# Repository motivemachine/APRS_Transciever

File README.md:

# APRS_Transciever
An in development design for a complete, standalone transciever for voice and aprs digital communication for the 2meter/70cm band. It is primarily based on the DRA818 radio module and controlled with an arduino. 

This project is made possible for amateur designers like me thanks to the work of:

markqvist and his APRS library:
https://github.com/markqvist/LibAPRS

darksidelemm and his DRA818 serial library:
https://github.com/darksidelemm/dra818

Progress:
Currently the basic Kicad schematic is complete, using an arduino nano and two bss183 mosfets to convert the 5v IO to 3.3v for the dRA818V. Resistors on Arduino Nano pins 4-7 form the DDS as used with LibAPRS. No other interfaces are yet included, but many are planned (gps, display, etc.)

Next steps:
After further breadboard testing, complete designs for the PCBs in Kicad. The first design will be for a single-sided PCB for etching at home and further development. A two layer production design will follow after any changes are made

Begin adding some other interfaces to the circuit, such as GPS, sh1106 OLED display, battery management circuits,and other useful telemetry

Firmware will mostly be based on the arduino libraries of others, but will be uploaded here as changes are made.

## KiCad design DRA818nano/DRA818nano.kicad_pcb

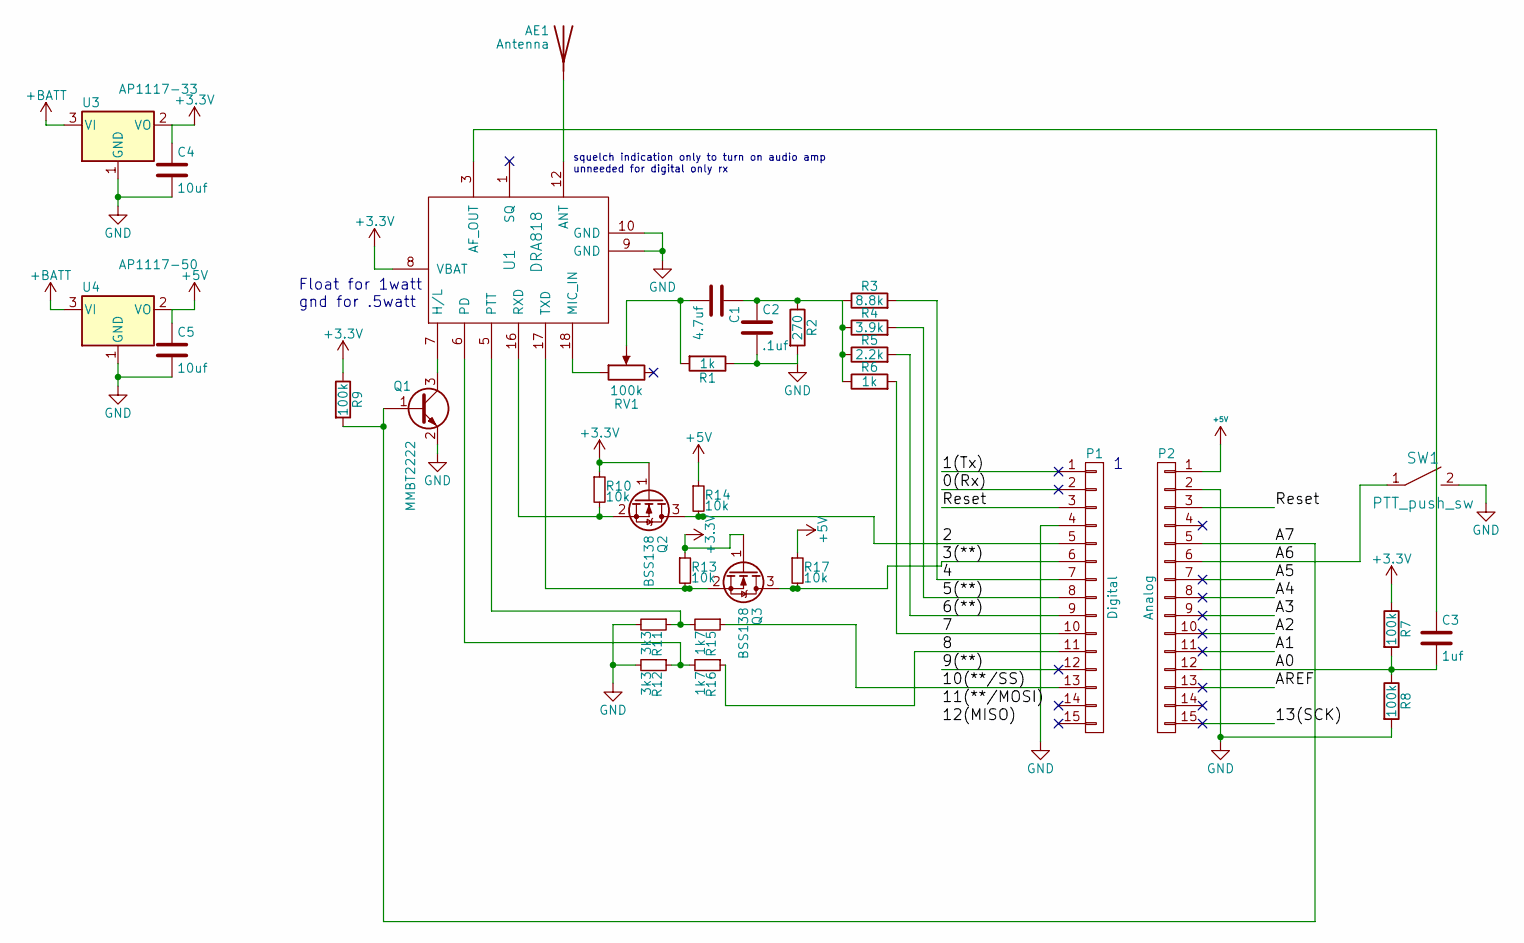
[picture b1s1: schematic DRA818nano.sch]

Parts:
AE1: Antenna; Pin_Header_Straight_1x01_Pitch2.54mm
C1: 4.7uf; C_0805
C2: .1uf; C_0805
C3: 1uf; C_0805
C4, C5: 10uf; C_0805
P1: Digital; Socket_Strip_Arduino_1x15
P2: Analog; Socket_Strip_Arduino_1x15
Q1: MMBT2222; SOT-23
Q2, Q3: BSS138; SOT-23
R1, R6: 1k; R_0805
R2: 270; R_0805
R3: 8.8k; R_0805
R4: 3.9k; R_0805
R5: 2.2k; R_0805
R7, R8, R9: 100k; R_0805
R10, R13, R14, R17: 10k; R_0805
R11, R12: 3k3; R_0805
R15, R16: 1k7; R_0805
RV1: 100k; Potentiometer_Trimmer_ACP_CA6v_Horizontal
SW1: PTT_push_sw; SW_PUSH_6mm_h7.3mm
U1: DRA818
U3: AP1117-33; SOT-223-3_TabPin2
U4: AP1117-50; SOT-223-3_TabPin2

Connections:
+3V3: C4.1, Q2.1 (G), Q3.1 (G), R7.1, R9.1, R10.1, R13.1, U1.8 (VBAT), U3.2 (VO)
+5V: C5.1, P2.1, R14.1, R17.1, U4.2 (VO)
+BATT: U3.3 (VI), U4.3 (VI)
/0(Rx): P1.2
/1(Tx): P1.1
/2: P1.5, Q2.3 (D), R14.2
/3(**): P1.6, Q3.3 (D), R17.2
/4: P1.7, R3.2
/5(**): P1.8, R4.2
/6(**): P1.9, R5.2
/7: P1.10, R6.2
/8: P1.11, R16.1
/9(**): P1.12
/10(**/SS): P1.13, R15.1
/13(SCK): P2.15
/A0: C3.2, P2.12, R7.2, R8.1
/A1: P2.11
/A2: P2.10
/A3: P2.9
/A4: P2.8
/A5: P2.7
/A6: P2.6, SW1.1
/A7: P2.5, Q1.1 (B), R9.2
/AREF: P2.13
/Reset: P1.3, P2.3
GND: C2.2, C4.2, C5.2, P1.4, P2.2, Q1.2 (E), R1.1, R2.2, R8.2, R11.2, R12.2, SW1.2, U1.9 (GND), U1.10 (GND), U3.1 (GND), U4.1 (GND)
unnamed: AE1.1, U1.12 (ANT)
unnamed: C1.1, C2.1, R2.1, R3.1, R4.1, R5.1, R6.1
unnamed: C1.2, R1.2, RV1.2
unnamed: C3.1, U1.3 (AF_OUT)
unnamed: Q1.3 (C), U1.7 (H/L)
unnamed: Q2.2 (S), R10.2, U1.16 (RXD)
unnamed: Q3.2 (S), R13.2, U1.17 (TXD)
unnamed: R11.1, R15.2, U1.5 (PTT)
unnamed: R12.1, R16.2, U1.6 (PD)
unnamed: RV1.1, U1.18 (MIC_IN)

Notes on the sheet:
Float for 1watt gnd for .5watt
squelch indication only to turn on audio amp unneeded for digital only rx

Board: 2 copper layers, 37 parts (0 on the bottom side), 26 nets, no tracks yet.

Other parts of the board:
P3, P4, P5, P6: CONN_01X01; 1pin_Nano

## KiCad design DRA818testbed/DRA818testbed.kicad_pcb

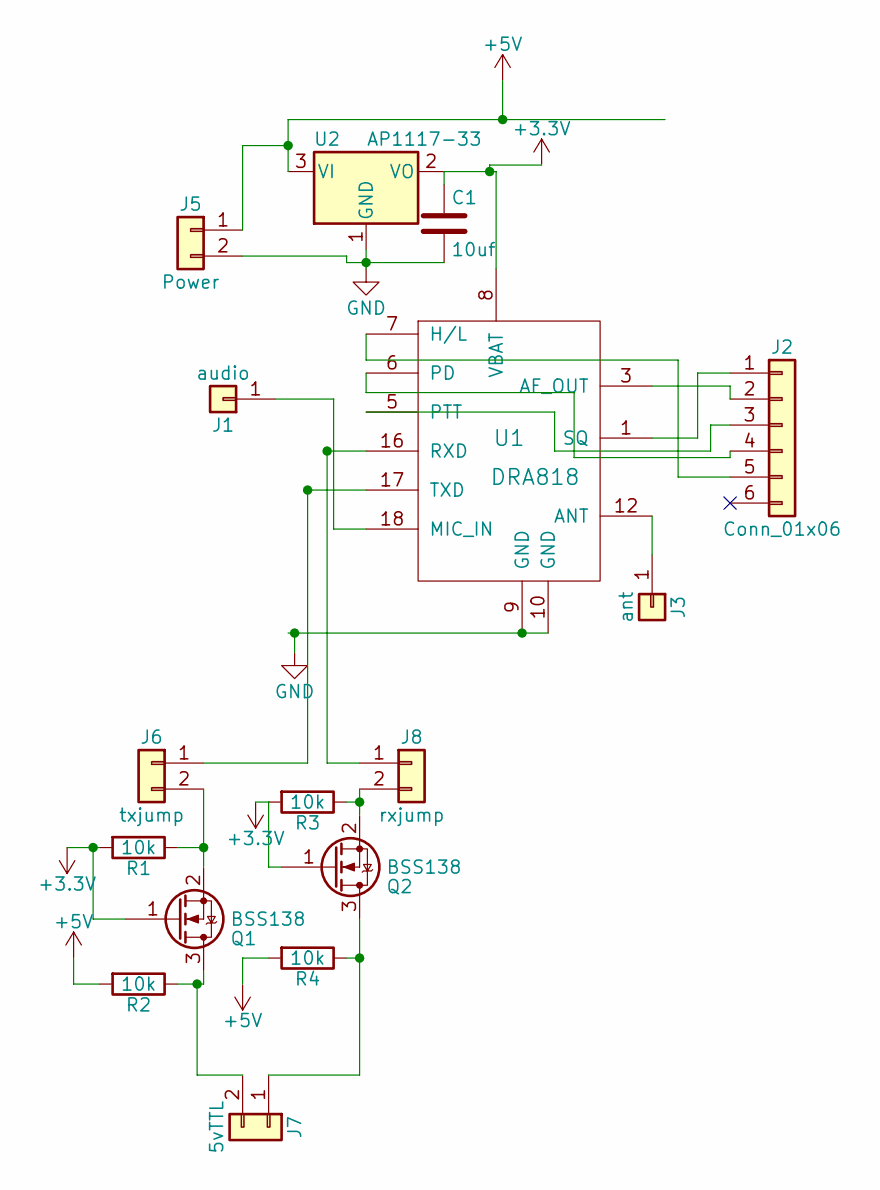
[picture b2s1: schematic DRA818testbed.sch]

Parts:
C1: 10uf; C_Disc_D8.0mm_W2.5mm_P5.00mm
J1: audio; Pin_Header_Straight_1x01_Pitch2.54mm
J2: Conn_01x06; Pin_Header_Straight_1x06_Pitch2.54mm
J3: ant; Pin_Header_Straight_1x01_Pitch2.54mm
J5: Power; Pin_Header_Straight_1x02_Pitch2.54mm
J6: txjump; Pin_Header_Straight_1x02_Pitch2.54mm
J7: 5vTTL; Pin_Header_Straight_1x02_Pitch2.54mm
J8: rxjump; Pin_Header_Straight_1x02_Pitch2.54mm
Q1, Q2: BSS138; SOT-23
R1, R2, R3, R4: 10k; R_0805
U1: DRA818
U2: AP1117-33; SOT-223-3_TabPin2

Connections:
+3V3: C1.1, Q1.1 (G), Q2.1 (G), R1.2, R3.2, U1.8 (VBAT), U2.2 (VO)
+5V: J5.1, R2.2, R4.2, U2.3 (VI)
GND: C1.2, J5.2, U1.9 (GND), U1.10 (GND), U2.1 (GND)
unnamed: J1.1, U1.18 (MIC_IN)
unnamed: J2.1, U1.1 (SQ)
unnamed: J2.2, U1.3 (AF_OUT)
unnamed: J2.3, U1.5 (PTT)
unnamed: J2.4, U1.6 (PD)
unnamed: J2.5, U1.7 (H/L)
unnamed: J3.1, U1.12 (ANT)
unnamed: J6.1, U1.17 (TXD)
unnamed: J6.2, Q1.2 (S), R1.1
unnamed: J7.1, Q2.3 (D), R4.1
unnamed: J7.2, Q1.3 (D), R2.1
unnamed: J8.1, U1.16 (RXD)
unnamed: J8.2, Q2.2 (S), R3.1

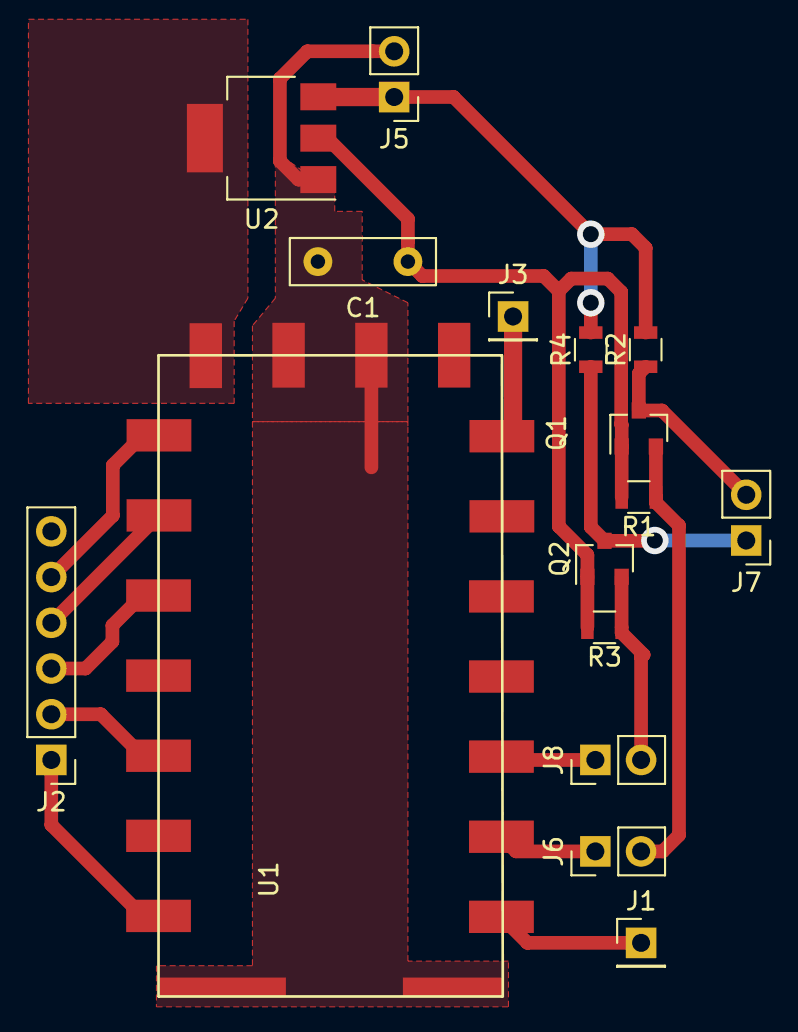
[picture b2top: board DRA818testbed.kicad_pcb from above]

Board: 2 copper layers, 16 parts (0 on the bottom side), 16 nets.

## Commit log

2018-04-13 Rename DRA818nano.kicad_pcb to Kicad/DRA818nano.kicad_pcb
2018-04-13 Rename DRA818nano.pro to Kicad/DRA818nano.pro
2018-04-13 Rename DRA818nano.sch to Kicad/DRA818nano.sch
2018-04-13 Rename DRA818nano.bak to Kicad/DRA818nano.bak
2018-04-13 Rename DRA818nano.net to Kicad/DRA818nano.net
2018-04-13 Rename DRA818nano-cache.lib to Kicad/DRA818nano-cache.lib
2018-04-13 Rename DRA818nano.cmp to Kicad/DRA818nano.cmp
2018-04-13 Reorganize existing files
2018-04-29 Added a test-board design
    Made a design to attach a dra818v to a breadboard, with a power regulator and level shifting mosfets. For easier testing with different UCs
2018-04-29 Updated logic level shift design
    Added BSS138 mosfets for TTL translation and a voltage divider for power down and PTT inputs.
